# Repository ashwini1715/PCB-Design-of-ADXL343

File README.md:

# PCB-Design-of-ADXL343
PCB Design of ADXL343 Accelerometer breakout board- Designed a customized PCB for the ADXL343 accelerometer by optimizing routing for I2C and SPI, resulting in improved signal integrity and communication performance. Enhanced solderability and heat management by applying thermal relief and conducting Design Rule Checks (DRC).

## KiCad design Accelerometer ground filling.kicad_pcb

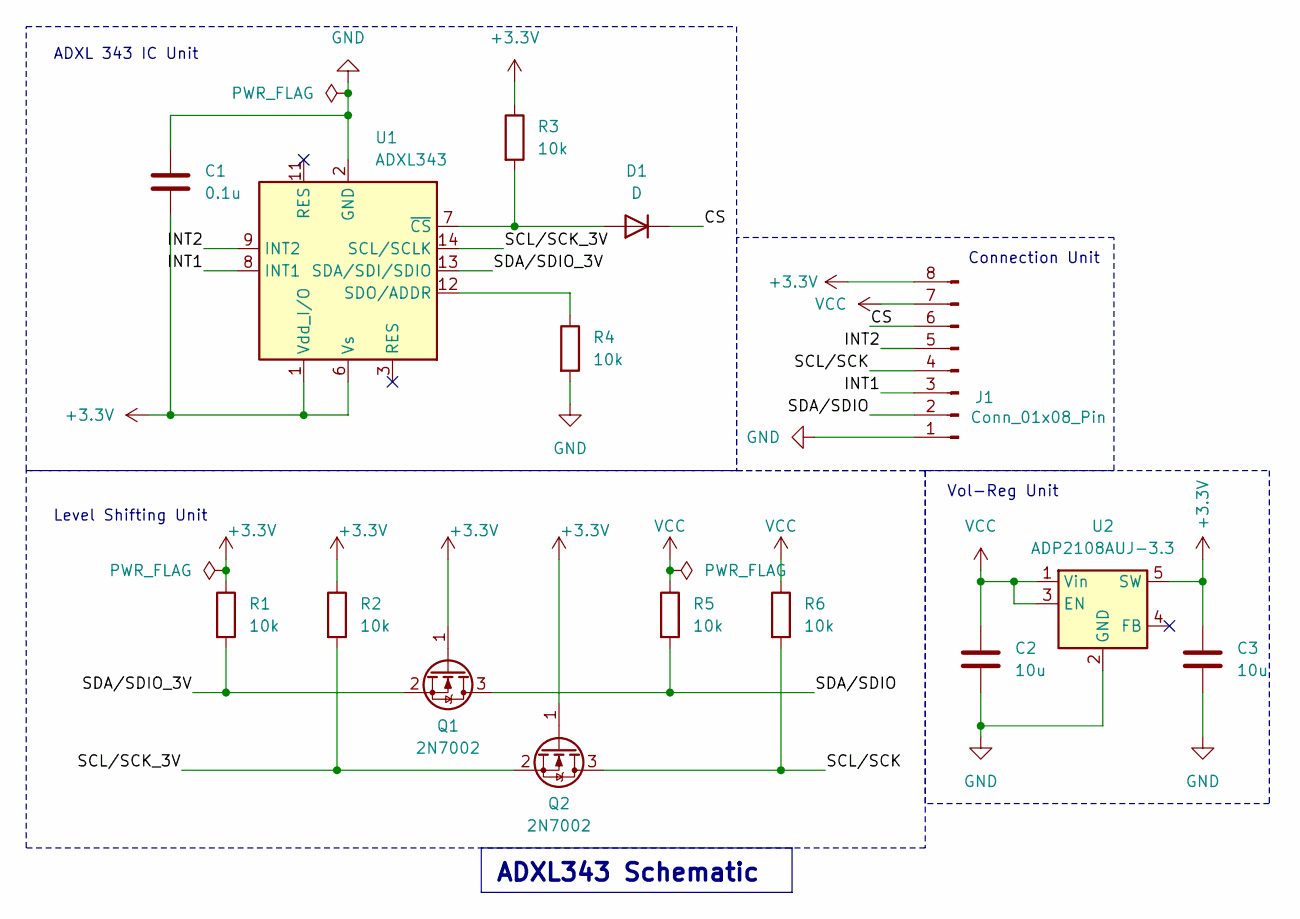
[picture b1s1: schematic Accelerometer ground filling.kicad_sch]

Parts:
C1: 0.1u; C_1206_3216Metric_Pad1.33x1.80mm_HandSolder
C2, C3: 10u; C_1206_3216Metric_Pad1.33x1.80mm_HandSolder
D1: D; D_0805_2012Metric_Pad1.15x1.40mm_HandSolder
J1: Conn_01x08_Pin; JST_EH_B8B-EH-A_1x08_P2.50mm_Vertical
Q1, Q2: 2N7002; SOT-23
R1, R2, R3, R4, R5, R6: 10k; R_1206_3216Metric_Pad1.30x1.75mm_HandSolder
U1: ADXL343; LGA-14_3x5mm_P0.8mm_LayoutBorder1x6y
U2: ADP2108AUJ-3.3; TSOT-23-5

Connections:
+3.3V: C1.2, C3.1, J1.8, Q1.1 (G), Q2.1 (G), R1.1, R2.1, R3.1, U1.1 (Vdd_I/O), U1.6 (Vs), U2.5 (SW)
/CS: D1.1 (K), J1.6
/INT1: J1.3, U1.8 (INT1)
/INT2: J1.5, U1.9 (INT2)
/SCL/SCK: J1.4, Q2.3 (D), R6.2
/SCL/SCK_3V: Q2.2 (S), R2.2, U1.14 (SCL/SCLK)
/SDA/SDIO: J1.2, Q1.3 (D), R5.2
/SDA/SDIO_3V: Q1.2 (S), R1.2, U1.13 (SDA/SDI/SDIO)
GND: C1.1, C2.2, C3.2, J1.1, R4.2, U1.2 (GND), U1.4 (GND), U1.5 (GND), U2.2 (GND)
unnamed: D1.2 (A), R3.2, U1.7 (~CS)
unnamed: R4.1, U1.12 (SDO/ADDR)
VCC: C2.1, J1.7, R5.1, R6.1, U2.1 (Vin), U2.3 (EN)

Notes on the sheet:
ADXL343 Schematic
Level Shifting Unit
Vol-Reg Unit
Connection Unit
ADXL 343 IC Unit

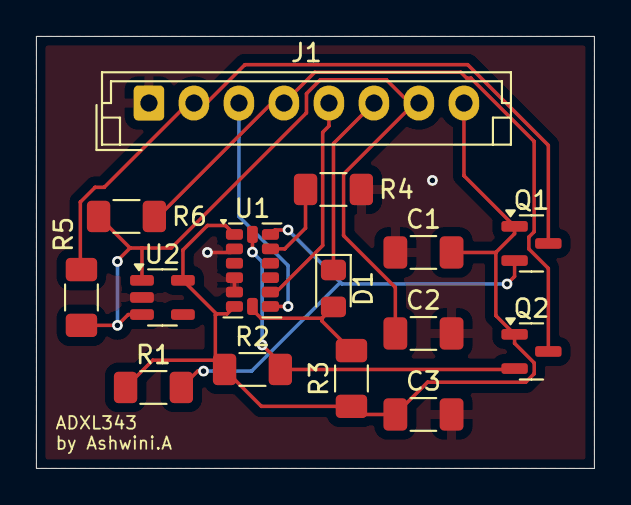
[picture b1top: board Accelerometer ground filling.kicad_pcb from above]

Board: 2 copper layers, 31.0 x 24.0 mm, 15 parts (0 on the bottom side), 12 nets.
